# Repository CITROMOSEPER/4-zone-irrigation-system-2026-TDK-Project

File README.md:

# Klímaváltozásra felkészített, adatvezérelt öntözőrendszer

Négyzónás, ESP32-alapú öntözővezérlő, amely a saját érzékelői és az időjárás-előrejelzés alapján dönti el, hogy egy zóna kapjon-e vizet, és ha igen, mennyit. Telefonról kezelhető, telepítés nélkül, és hálózat nélkül is működik.

A repository a teljes projektet tartalmazza: a firmware-t, a webes felületet, a KiCad-terveket, a szimulációt, az előrejelzés-kutatást, valamint a TDK-dolgozatot és a hozzá tartozó dokumentumokat.

A projekt az Óbudai Egyetem Kandó Kálmán Villamosmérnöki Karán készült (2026 ősz).

**Szerzők:** [Nemes Dániel](https://github.com/CITROMOSEPER), [Nyul Balázs](https://github.com/snotor)

**Konzulens:** [Sándor Tamás](https://uni-obuda.hu/szemely/sandor-tamas/)

## Tartalom

| Mappa vagy fájl | Tartalom |
|---|---|
| [`Final PlatformIO code/Irrigation system/`](Final%20PlatformIO%20code/Irrigation%20system/) | **Végleges firmware (v1.3.2)**, webes felület, PC-s és böngészős tesztek, dokumentáció |
| [`Forecast research/`](Forecast%20research/) | Négy időjárási modell egyhónapos összevetése egy közeli állomás méréseivel |
| [`szimulacio/`](szimulacio/) | A döntési logika Python-szimulációja négy budapesti idényre |
| [`Áramkör/Öntözőberendezés/`](Áramkör/Öntözőberendezés/) | KiCad kapcsolási rajz és NYÁK-terv, biztonsági mentésekkel |
| [`Rendszertervek/`](Rendszertervek/) | Az eredeti logikai és fizikai rendszerterv (a koncepció korábbi állapota) |
| [`Arduino - Irrigation system - final/`](Arduino%20-%20Irrigation%20system%20-%20final/) | A firmware 1.0.0-s állapota (2026. október 31.) |
| [`Arduino - discontinued/`](Arduino%20-%20discontinued/) | Lezárt első firmware, USB-s kapcsolattal |
| [`Python App - discontinued/`](Python%20App%20-%20discontinued/) | Lezárt PC-s kezelőprogram az első firmware-hez |
| [`TDK_dolgozat_ND_NyB.docx`](TDK_dolgozat_ND_NyB.docx) | A TDK-dolgozat |
| [`TDK_tesztjegyzokonyv_ND_NyB.docx`](TDK_tesztjegyzokonyv_ND_NyB.docx) | Kitöltött tesztjegyzőkönyv a makett vizsgálatairól |
| [`TDK_szimulacios_jegyzokonyv_ND_NyB.docx`](TDK_szimulacios_jegyzokonyv_ND_NyB.docx) | Szimulációs jegyzőkönyv |
| [`TDK_MI_nyilatkozat_ND_NyB.docx`](TDK_MI_nyilatkozat_ND_NyB.docx) | Nyilatkozat a mesterséges intelligencia használatáról |
| [`TDK_bemutato_ND_NyB.docx`](TDK_bemutato_ND_NyB.docx) | A TDK-téma rövid bemutatója |
| [`Kreatív megoldások – prezentáció.pptx`](Kreatív%20megoldások%20–%20prezentáció.pptx) | A tárgyi előadás diái |

## Funkciók

- 4 független zóna, zónánként saját naptárral, növény-, talaj- és szórófej-beállítással
- 3 üzemmód: ütemezett, érzékelő alapú (talajszenzoros) és időjárás alapú (szenzor nélküli, FAO-56 vízmérleg)
- Számolt vízadag a talaj vízhiányából, a FAO-56 fejlődési szakaszaival (változó Kc és gyökérmélység)
- Másodperc pontosságú futásidő és szakaszos öntözés (cycle and soak), zónánkénti térfogatárammal
- Esőtiltás két modell (DWD ICON és ECMWF) egyezése alapján a következő 24 órára; internet nélkül Hargreaves-becslés a helyi hőmérsékletből
- Mobilos webes felület, amelyet maga az eszköz szolgál ki; statisztika, napló, kétnyelvű (magyar, angol), világos és sötét téma
- Biztonsági réteg: szelep és szivattyú sorrendje, tartályszint, futásidő, napi keret, watchdog
- Áramszünet után a megszakadt öntözés naplózása és egyszeri folytatása, a hibás órakiolvasások szűrése
- Tiltási időszakok, fagy- és hidegvédelem, téli mód, nyomógombos vezérlés, hangjelzések

## Hardver

| Egység | Típus |
|---|---|
| Vezérlő | ESP32-WROOM-32 fejlesztőlap |
| Talajnedvesség | HW-390, 4 db |
| Tartályszint | HC-SR04 |
| Eső | SA-28 |
| Hőmérséklet, páratartalom | BME280 |
| Valós idejű óra | DS1302 |
| Relék | G2RL-1, 5 db |
| Szelepek | SF-02-12V, 4 db |
| Szivattyú | AD5P-PUMP-H-BK |
| Táp | 12 V DC, 5 V-os kapcsolóüzemű átalakítóval |

A makett teljes anyagköltsége 43 553 Ft. A végleges lábkiosztás a [`PINS.h`](Final%20PlatformIO%20code/Irrigation%20system/include/PINS.h) fájlban található. A KiCad-terv egy korábbi firmware-hez készült, ezért a végleges lábkiosztástól több ponton eltér; az eltéréseket a dolgozat 7.6. alfejezete sorolja fel.

## Firmware fordítása és feltöltése

Ehhez [PlatformIO](https://platformio.org/) szükséges. A parancsokat a `Final PlatformIO code/Irrigation system` mappából kell futtatni:

```bash
pio run -t upload
```

```bash
pio device monitor
```

Első indításkor az eszköz `Irrigation-Setup-XXXX` nevű nyílt Wi-Fi-hálózatot hoz létre. A beállító oldal a `http://10.73.0.1/` címen érhető el, és a csatlakozás után kiírja a vezérlő IP-címét. Utána a felület az `irrigation.local` címen is elérhető.

A firmware részletes leírása a [firmware README-jében](Final%20PlatformIO%20code/Irrigation%20system/README.md), a változások a [CHANGELOG-ban](Final%20PlatformIO%20code/Irrigation%20system/CHANGELOG.md), az API a [`docs/API.md`](Final%20PlatformIO%20code/Irrigation%20system/docs/API.md) fájlban, a fejlesztés története a [`docs/TDK-coding-journey.md`](Final%20PlatformIO%20code/Irrigation%20system/docs/TDK-coding-journey.md) fájlban található.

## Webes felület kipróbálása

A [`portal/app-demo.html`](Final%20PlatformIO%20code/Irrigation%20system/portal/app-demo.html) fájlt letöltés után böngészőben megnyitva a felület hardver nélkül kipróbálható. A megjelenő adatok szimuláltak.

## Tesztek

A firmware PC-re is lefordítható, a hardvert csonkok helyettesítik. Az 1.3.2-es készlet 403 ellenőrzést tartalmaz, a futtatáshoz `g++` és POSIX-környezet kell (Linux, WSL vagy Git Bash). A parancsokat a firmware mappájából kell indítani:

```bash
git clone --depth 1 -b v7.4.2 https://github.com/bblanchon/ArduinoJson.git /tmp/aj
```

```bash
test/host/build.sh /tmp/aj/src
```

A webes felület böngészős tesztjei (321 ellenőrzés) Pythonnal és Playwrighttal futnak:

```bash
pip install playwright && playwright install chromium
```

```bash
test/ui/run.sh
```

A 2026. november 7-i kódellenőrzéskor mind a 403, mind a 321 ellenőrzés hibátlanul lefutott.

## Eredmények

### Makett (2026. 11. 06–07.)

- A tíz funkcionális tesztből kilenc megfelelt, egy részben (a visszacsatolásos adagnál a talaj nem száradt az alsó határ alá).
- Mért térfogatáram zónánként: 1,07 / 0,62 / 0,80 / 0,96 L/perc.
- A tartályszint-mérés eltérése a vonalzós értéktől: 0,05–0,24 cm.

### Előrejelzés-összevetés (2026. 10. 09. – 11. 07.)

- 27 kiértékelt nap, 49,1 mm eső, 6 csapadékos nap, referencia egy kb. 900 m-re lévő amatőr állomás.
- A hőmérsékletet az ECMWF és a MET Norway jelezte előre a legpontosabban (1,5 °C átlagos hiba), a GFS 2,5 °C-kal melegebbet jelzett.
- A következő 24 órára az ICON mind a 6 csapadékos napot előre jelezte; 5–7 napos távon a csapadék-előrejelzés gyakorlatilag zaj.

A kiértékelés újrafuttatható a `Forecast research` mappából:

```bash
python compare.py
```

### Szimuláció (2022–2025, Budapest)

A szkriptek Python 3-mal, külső csomag nélkül futnak, a `szimulacio` mappából:

```bash
python sim.py
```

Az eredmények számított, nem mért értékek:

| Összehasonlítás a fix időzítőhöz | Vízmegtakarítás |
|---|---|
| Csak esőtiltás | 21% |
| Számolt adag, pázsit | 50–52% |
| Számolt adag, zöldség | 34–35% |
| Számolt adag, mediterrán növény | 75–76% |

## Ismert korlátok

- A webes felületnek nincs hitelesítése, ezért a helyi hálózaton bárki elérheti.
- Az időjárási lekérés nem ellenőrzi a TLS-tanúsítványt.
- Áramlásmérő nincs: a liter a szivattyúidő és a kimért térfogatáram szorzata.
- A talajszenzorok közös, közelítő kalibrációval futnak, a százalék relatív nedvességindex.
- Nincs távoli firmware-frissítés (OTA), és a NYÁK a végleges firmware-hez módosítást igényel.

## Mesterséges intelligencia használata

A firmware, a webes felület és a Python-alkalmazás a Claude Opus 5.5 modell segítségével készült, a dolgozat szövegének nagy része, a szimuláció és a jegyzőkönyvek szintén. A kapcsolási rajzhoz és a nyomtatott áramkörhöz nem használtunk MI-eszközt. A részleteket a dolgozat 12.4. alfejezete és az MI-nyilatkozat tartalmazza.

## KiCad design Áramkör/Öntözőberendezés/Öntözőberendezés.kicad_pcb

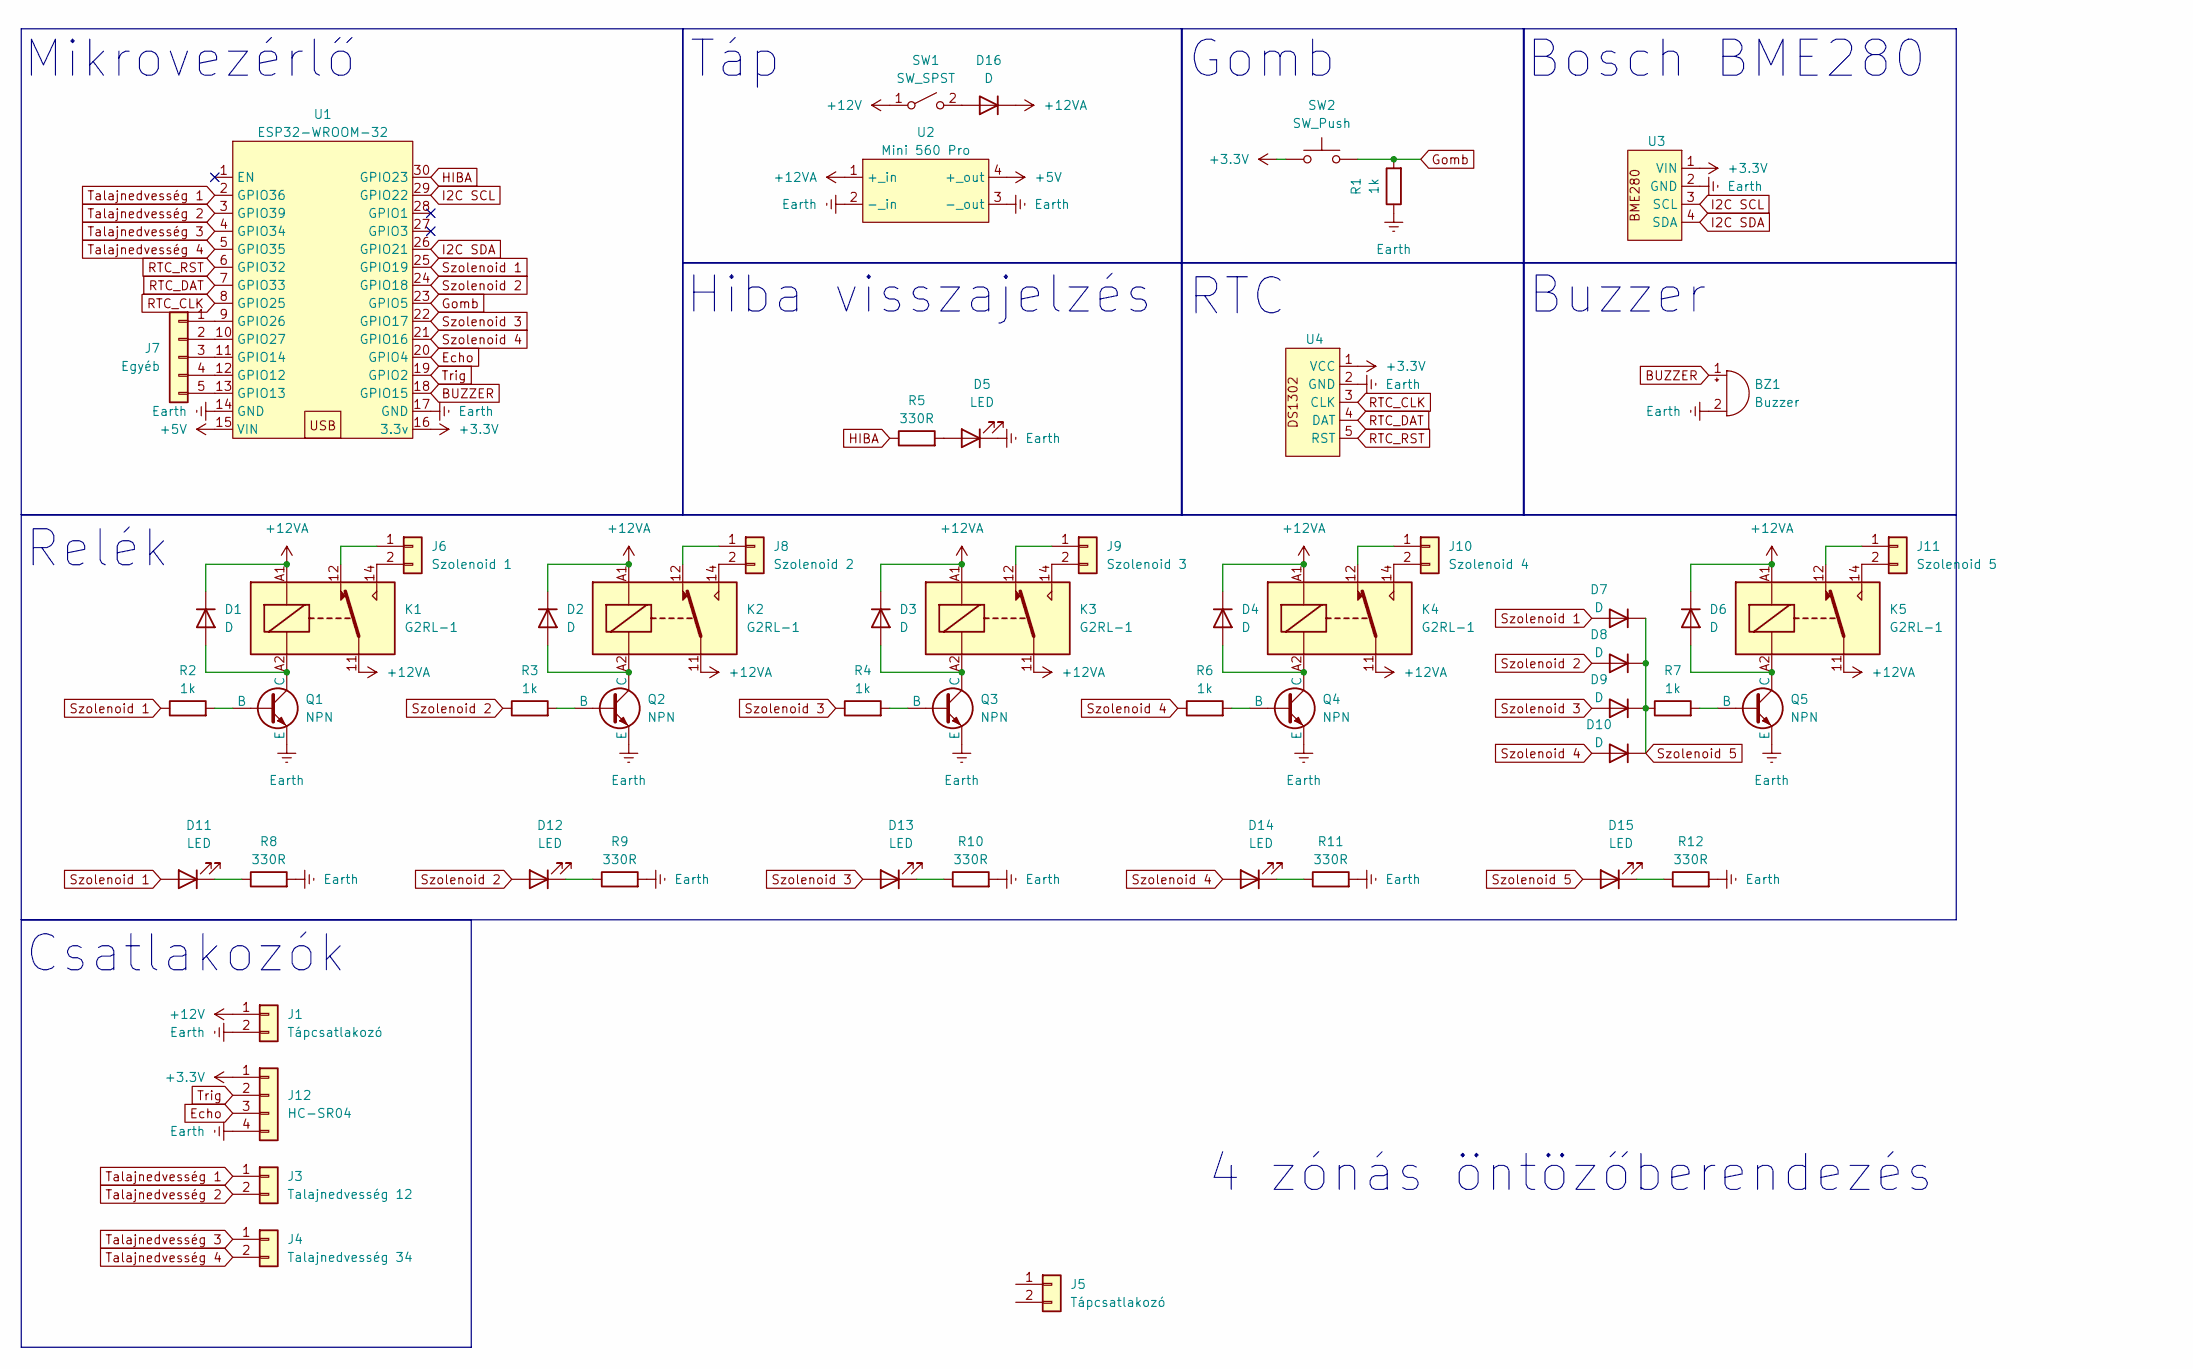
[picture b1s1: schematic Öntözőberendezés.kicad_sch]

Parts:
BZ1: Buzzer; Passive buzzer 17mm
D1, D2, D3, D4, D6, D7, D8, D9, D10: D; D_DO-41_SOD81_P10.16mm_Horizontal
D5, D11, D12, D13, D14, D15: LED; PinHeader_1x02_P2.54mm_Vertical
D16: D; D_DO-41_SOD81_P2.54mm_Vertical_KathodeUp
J1: Tápcsatlakozó; PinHeader_1x02_P2.54mm_Vertical
J3: Talajnedvesség 12; PinHeader_1x02_P2.54mm_Vertical
J4: Talajnedvesség 34; PinHeader_1x02_P2.54mm_Vertical
J5: Tápcsatlakozó; TerminalBlock_4Ucon_1x02_P3.50mm_Horizontal
J6: Szolenoid 1; PinHeader_1x02_P2.54mm_Vertical
J7: Egyéb; PinHeader_1x05_P2.54mm_Vertical
J8: Szolenoid 2; PinHeader_1x02_P2.54mm_Vertical
J9: Szolenoid 3; PinHeader_1x02_P2.54mm_Vertical
J10: Szolenoid 4; PinHeader_1x02_P2.54mm_Vertical
J11: Szolenoid 5; PinHeader_1x02_P2.54mm_Vertical
J12: HC-SR04; PinHeader_1x04_P2.54mm_Vertical
K1, K2, K3, K4, K5: G2RL-1; Relay_SPDT_Omron_G2RL-1
Q1, Q2, Q3, Q4, Q5: NPN; TO-92L_Inline_Wide
R1, R2, R3, R4, R6, R7: 1k; R_Axial_DIN0207_L6.3mm_D2.5mm_P7.62mm_Horizontal
R5, R8, R9, R10, R11, R12: 330R; R_Axial_DIN0207_L6.3mm_D2.5mm_P7.62mm_Horizontal
SW1: SW_SPST; PinHeader_1x02_P2.54mm_Vertical
SW2: SW_Push; PinHeader_1x02_P2.54mm_Vertical
U1: ESP32-WROOM-32; ESP-WROOM-32
U2: Mini 560 Pro; Mini 560 PRO buck converter
U3: PinHeader_1x04_P2.54mm_Vertical
U4: DS1302 module

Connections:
+3.3V: J12.1, SW2.1, U1.16 (3.3v), U3.1 (VIN), U4.1 (VCC)
+5V: U1.15 (VIN), U2.4 (+_out)
+12V: J1.1, SW1.1 (A)
+12VA: D1.1 (K), D2.1 (K), D3.1 (K), D4.1 (K), D6.1 (K), D16.1 (K), K1.11, K1.A1, K2.11, K2.A1, K3.11, K3.A1, K4.11, K4.A1, K5.11, K5.A1, U2.1 (+_in)
BUZZER: BZ1.1 (+), U1.18 (GPIO15)
Earth: BZ1.2 (-), D5.1 (K), J1.2, J12.4, Q1.3 (E), Q2.3 (E), Q3.3 (E), Q4.3 (E), Q5.3 (E), R1.1, R8.2, R9.2, R10.2, R11.2, R12.2, U1.14 (GND), U1.17 (GND), U2.2 (-_in), U2.3 (-_out), U3.2 (GND), U4.2 (GND)
Echo: J12.3, U1.20 (GPIO4)
Gomb: R1.2, SW2.2, U1.23 (GPIO5)
HIBA: R5.1, U1.30 (GPIO23)
I2C SCL: U1.29 (GPIO22), U3.3 (SCL)
I2C SDA: U1.26 (GPIO21), U3.4 (SDA)
unnamed: D1.2 (A), K1.A2, Q1.1 (C)
unnamed: D2.2 (A), K2.A2, Q2.1 (C)
unnamed: D3.2 (A), K3.A2, Q3.1 (C)
unnamed: D4.2 (A), K4.A2, Q4.1 (C)
unnamed: D5.2 (A), R5.2
unnamed: D6.2 (A), K5.A2, Q5.1 (C)
unnamed: D11.1 (K), R8.1
unnamed: D12.1 (K), R9.1
unnamed: D13.1 (K), R10.1
unnamed: D14.1 (K), R11.1
unnamed: D15.1 (K), R12.1
unnamed: D16.2 (A), SW1.2 (B)
unnamed: J6.1, K1.12
unnamed: J6.2, K1.14
unnamed: J7.1, U1.9 (GPIO26)
unnamed: J7.2, U1.10 (GPIO27)
unnamed: J7.3, U1.11 (GPIO14)
unnamed: J7.4, U1.12 (GPIO12)
unnamed: J7.5, U1.13 (GPIO13)
unnamed: J8.1, K2.12
unnamed: J8.2, K2.14
unnamed: J9.1, K3.12
unnamed: J9.2, K3.14
unnamed: J10.1, K4.12
unnamed: J10.2, K4.14
unnamed: J11.1, K5.12
unnamed: J11.2, K5.14
unnamed: Q1.2 (B), R2.2
unnamed: Q2.2 (B), R3.2
unnamed: Q3.2 (B), R4.2
unnamed: Q4.2 (B), R6.2
unnamed: Q5.2 (B), R7.2
RTC_CLK: U1.8 (GPIO25), U4.3 (CLK)
RTC_DAT: U1.7 (GPIO33), U4.4 (DAT)
RTC_RST: U1.6 (GPIO32), U4.5 (RST)
Szolenoid 1: D7.2 (A), D11.2 (A), R2.1, U1.25 (GPIO19)
Szolenoid 2: D8.2 (A), D12.2 (A), R3.1, U1.24 (GPIO18)
Szolenoid 3: D9.2 (A), D13.2 (A), R4.1, U1.22 (GPIO17)
Szolenoid 4: D10.2 (A), D14.2 (A), R6.1, U1.21 (GPIO16)
Szolenoid 5: D7.1 (K), D8.1 (K), D9.1 (K), D10.1 (K), D15.2 (A), R7.1
Talajnedvesség 1: J3.1, U1.2 (GPIO36)
Talajnedvesség 2: J3.2, U1.3 (GPIO39)
Talajnedvesség 3: J4.1, U1.4 (GPIO34)
Talajnedvesség 4: J4.2, U1.5 (GPIO35)
Trig: J12.2, U1.19 (GPIO2)

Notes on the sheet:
Hiba visszajelzés
Gomb
Mikrovezérlő
Buzzer
4 zónás öntözőberendezés
Csatlakozók
Bosch BME280
Relék
Táp
RTC

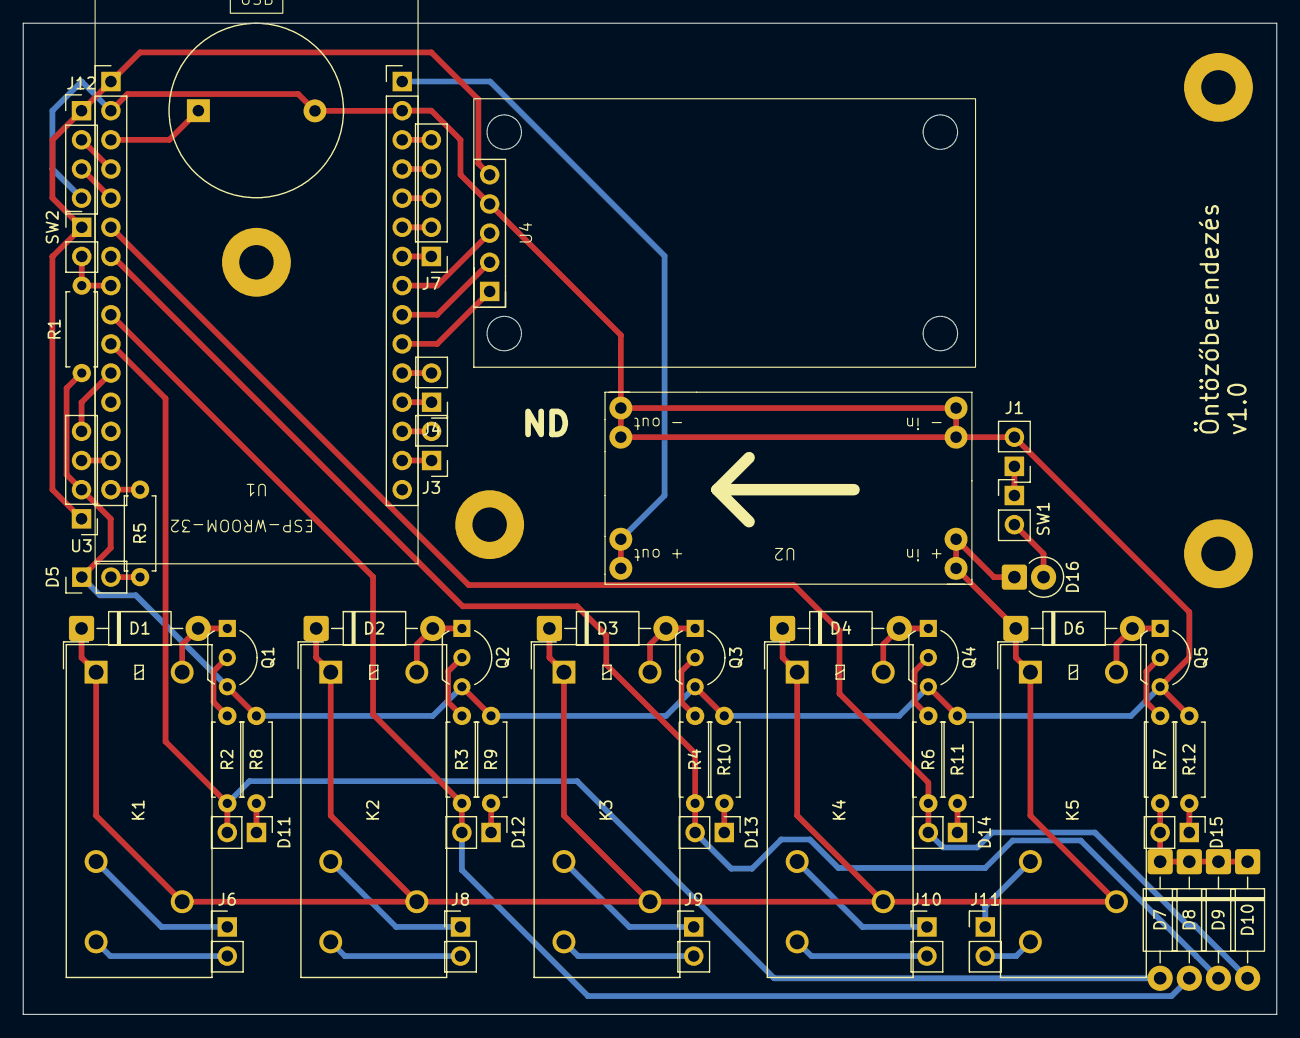
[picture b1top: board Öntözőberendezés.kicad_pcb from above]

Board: 2 copper layers, 109.2 x 86.4 mm, 55 parts (0 on the bottom side), 56 nets.

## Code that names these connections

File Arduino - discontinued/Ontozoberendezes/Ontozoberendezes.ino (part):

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const float TANK_MIN_SPAN_CM = 5.0f;         // high and low level must be at least this far apart
const float WATER_LOW_ON_PERCENT = 10.0f;    // the error LED turns on below this level ...
const float WATER_LOW_OFF_PERCENT = 12.0f;   // ... and off again above this one (so it does not flicker at the edge)
const uint32_t ECHO_TIMEOUT_US = 30000UL;    // no echo within 30 ms (about 5 m) means no measurement
const uint8_t WATER_MAX_FAILS = 5;           // this many failed measurements in a row (one per second) = sensor lost

const uint32_t SCHED_INTERVAL_MS = 1000;                   // the whole timetable is re-evaluated this often
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float WATER_DISTANCE_CM = 0;             // sensor to water surface, the water level in centimeters
float WATER_PERCENT = 0;                 // 0 % = low level, 100 % = high level
bool WATER_VALID = false;                // there is a recent reading
uint8_t WATER_FAILS = 0;                 // measurements in a row without a usable echo
volatile bool WATER_LOW_ALERT = false;   // close to empty: the error LED stays on

Adafruit_BME280 bme;
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
// ----- Fetched time & date (pool.ntp.org, DS1302) -------------------------------------------------------------------

ThreeWire rtcWire(RTC_DAT_PIN, RTC_CLK_PIN, RTC_RST_PIN);
RtcDS1302<ThreeWire> Rtc(rtcWire);

volatile TimeSource timeSource = TS_NONE;
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void BUZZER_INIT()
{
#if defined(ESP_ARDUINO_VERSION_MAJOR) && ESP_ARDUINO_VERSION_MAJOR >= 3
  ledcAttach(BUZZER_PIN, 2000, 8);
  ledcWriteTone(BUZZER_PIN, 0);
#else
  ledcSetup(BUZZER_LEDC_CHANNEL, 2000, 8);
  ledcAttachPin(BUZZER_PIN, BUZZER_LEDC_CHANNEL);
  ledcWriteTone(BUZZER_LEDC_CHANNEL, 0);
#endif
}
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void BUZZER_TONE(uint16_t hz)   // 0 = silence
{
#if defined(ESP_ARDUINO_VERSION_MAJOR) && ESP_ARDUINO_VERSION_MAJOR >= 3
  ledcWriteTone(BUZZER_PIN, hz);
#else
  ledcWriteTone(BUZZER_LEDC_CHANNEL, hz);
#endif
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  APPLY_OUTPUTS();   // everything off

  pinMode(ERROR_LED_PIN, OUTPUT);
  pinMode(BUZZER_PIN, OUTPUT);
  BUZZER_INIT();

  // Power-up self test: LED flash and boot chime. If you do not see/hear them, the problem is wiring or the buzzer type
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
